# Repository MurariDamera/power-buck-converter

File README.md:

me · MD
# LM2596 Buck Converter — 12 V → 5 V
 
A fixed-output 5 V step-down (buck) converter built around the **LM2596T-5.0** switching regulator, designed in **KiCad 10**. Two-layer through-hole board, 71 × 45 mm, with ground pours on both layers and four M3 mounting holes.
 
This is a prototype design reproduced from a LM2596 design guide. It passes KiCad's electrical and design-rule checks, and the power stage has been verified in LTspice against TI's transient model (see [Simulation](#simulation)) — but it has **not** been prototyped or thermally tested. See [Operating limits](#operating-limits) before building.
 
## Design summary
 
| Parameter | Value |
| --- | --- |
| Regulator | LM2596T-5.0 (fixed 5 V, 150 kHz) |
| Input | 12 V nominal |
| Output | 5 V |
| Output target | 3 A (design target, not a validated rating) |
| Board | 71 × 45 mm, 2 layers, 1.6 mm nominal |
| Mounting | 4 × 3.2 mm M3 holes |
 
Power tracks are 1.25–1.5 mm with a short 0.9 mm switch-pin escape. Both copper layers have GND zones. A 0.35 mm bottom-layer trace carries feedback directly from C3's positive pad. U1 sits near the top edge to allow an external heatsink (heatsink not yet selected).
 
## Bill of materials
 
| Ref | Value | Footprint |
| --- | --- | --- |
| U1 | LM2596T-5.0 | TO-220-5 staggered (Package_TO_SOT_THT) |
| J1 | 12 V input | Phoenix MKDS 5.08 mm 1×02 |
| J2 | 5 V output | Phoenix MKDS 5.08 mm 1×02 |
| C1 | 680 µF / 35 V | CP_Radial D10 mm P5 mm |
| C2 | 100 nF / 50 V | C_Disc D5 mm P5 mm |
| C3 | 220 µF / 25 V | CP_Radial D8 mm P3.5 mm |
| D1 | 1N5822 | DO-201AD P15.24 mm |
| L1 | 33 µH, Isat ≥ 3.5 A | L_Radial D12.5 mm P7 mm |
| H1–H4 | M3 mounting hole | MountingHole 3.2 mm |
 
C1/C2/C3 correspond to Cin/Cin2/Cout in the source guide. No adjustable-output divider is fitted.
 
## Connections
 
| Net | Connected pins |
| --- | --- |
| VIN | J1.1, C1.1, C2.1, U1.1 |
| SW | U1.2, D1.1 (cathode/band), L1.1 |
| +5V | L1.2, C3.1, J2.1, U1.4 (FB) |
| GND | J1.2, C1.2, C2.2, U1.3, U1.5, D1.2 (anode), C3.2, J2.2 |
 
J1 pin 1 is input positive; J2 pin 1 is output positive; both pin 2 terminals are ground. Follow the `+` markings on the electrolytic footprints and the cathode band on D1. U1 uses the staggered TO-220-5 footprint, not a straight five-pin footprint.
 
## Files
 
- `Buck_Converter.kicad_pro` — project file. Open this in KiCad, then double-click the schematic or PCB.
- `Buck_Converter.kicad_sch` — schematic.
- `Buck_Converter.kicad_pcb` — placed, routed board with filled ground zones.
- `sym-lib-table`, `fp-lib-table` — library tables (reference standard KiCad 10 libraries).
- `ltspice/` — LTspice validation of the power stage. `Buck_Converter_LTspice.asc` is the schematic (open it and hit Run); `LM2596_5P0_TRANS.lib` is TI's official LM2596-5.0 transient model, ported from PSpice syntax; `LM2596_5P0_TRANS.asy` is the matching symbol; `Buck_Converter_LTspice.plt` restores the plot panes. All four files must stay together in the same folder.
 
## Validation
 
KiCad 10.0.6 ERC and DRC (with zone refill and schematic parity) both report zero violations, zero unconnected items, and zero parity issues, with no rule exclusions.
 
These checks verify CAD connectivity and geometry only — no prototype measurement or thermal test has been performed.
 
## Simulation
 
The power stage (D1, L1, C1–C3) plus TI's official LM2596-5.0 PSpice transient model were simulated in LTspice (`ltspice/Buck_Converter_LTspice.asc`), 12 V in, 150 kHz switching, transient analysis to steady state:
 
| Load | Simulated output |
| --- | --- |
| 1 A (5 Ω) | 4.99 V |
| 3 A design target (1.667 Ω) | 4.31 V, 120 mV ripple |
 
At the 3 A design target the loop sags to 4.31 V instead of regulating to 5.0 V. This is a real result, not a simulation artifact — it was confirmed by checking that regulation is accurate at light load (1 A) and only degrades as load approaches the design target, consistent with [Operating limits](#operating-limits) already flagging 3 A as unvalidated. Treat 3 A as the point where this design's regulation margin runs out, not as a safe operating current.
 
This is a transient-model simulation, not a hardware measurement — it doesn't account for PCB parasitics, the specific 1N5822's real diode curve, or thermal effects.
 
## Operating limits
 
- **12 V nominal input only** — C1 (35 V) and D1 (40 V) don't support the guide's 7–40 V range.
- **3 A is an unvalidated target** — LTspice shows regulation sagging to 4.31 V at 3 A vs. 4.99 V at 1 A ([Simulation](#simulation)), and the 1N5822 falls short of TI's recommended 3.9 A diode rating at that load.
- Verify real part ratings/footprints before ordering, and bring the board up on a current-limited supply, unloaded first.
 
## Source
 
Reproduced from the LM2596 buck converter design guide, cross-referenced against the [Texas Instruments LM2596 datasheet, Rev. G](https://www.ti.com/lit/ds/symlink/lm2596.pdf) (§9.2.1 and §9.4).

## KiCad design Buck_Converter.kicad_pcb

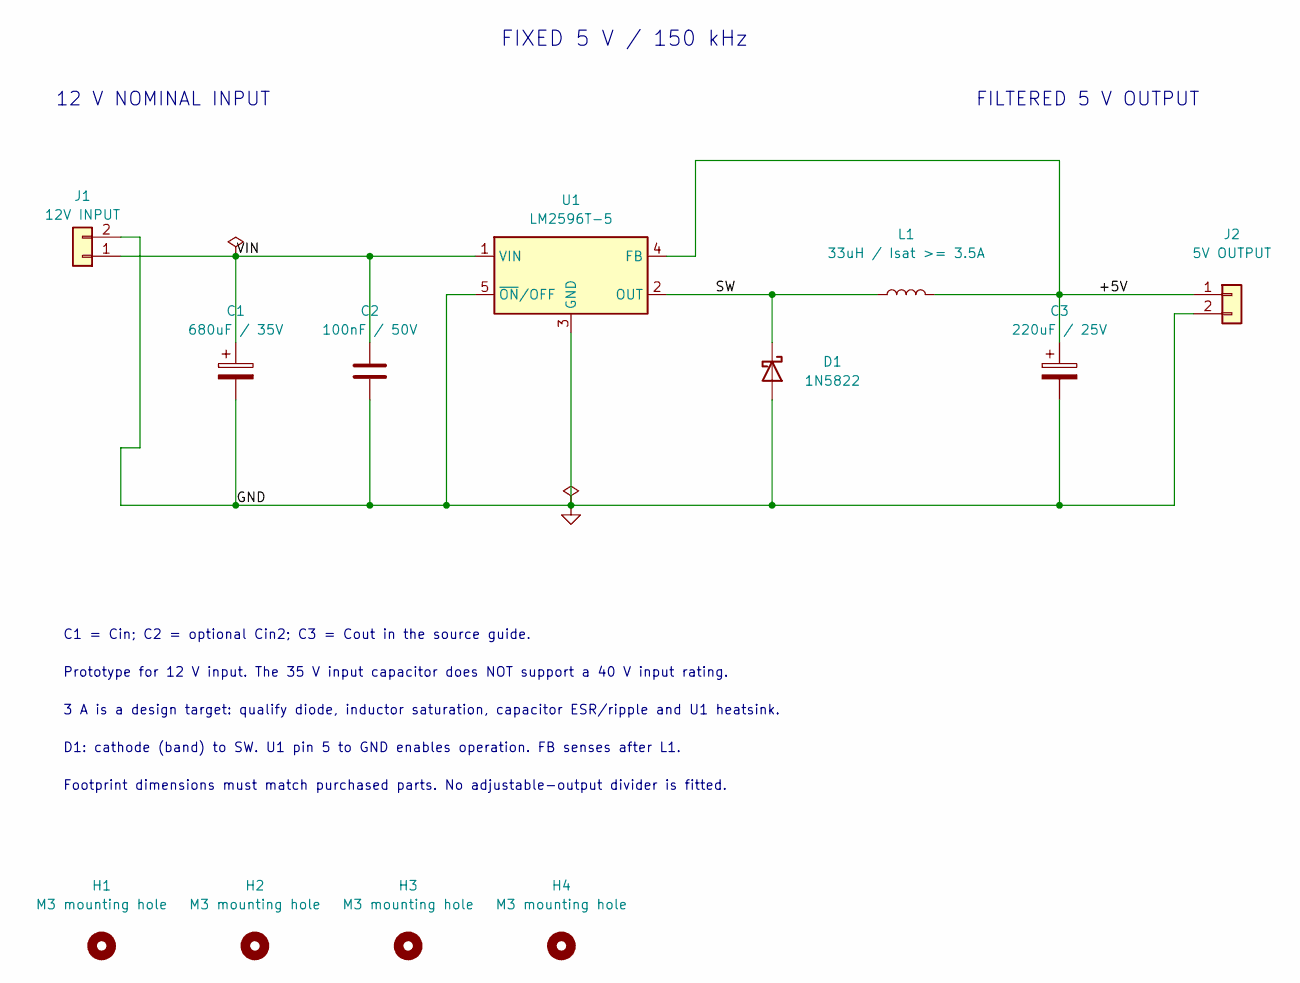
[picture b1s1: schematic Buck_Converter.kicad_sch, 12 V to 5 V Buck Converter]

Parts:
C1: 680uF / 35V; CP_Radial_D10.0mm_P5.00mm
C2: 100nF / 50V; C_Disc_D5.0mm_W2.5mm_P5.00mm
C3: 220uF / 25V; CP_Radial_D8.0mm_P3.50mm
D1: 1N5822; D_DO-201AD_P15.24mm_Horizontal
H1, H2, H3, H4: M3 mounting hole; MountingHole_3.2mm_M3
J1: 12V INPUT; TerminalBlock_Phoenix_MKDS-1,5-2-5.08_1x02_P5.08mm_Horizont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
J2: 5V OUTPUT; TerminalBlock_Phoenix_MKDS-1,5-2-5.08_1x02_P5.08mm_Horizont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
L1: 33uH / Isat >= 3.5A; L_Radial_D12.5mm_P7.00mm_Fastron_09HCP
U1: LM2596T-5; TO-220-5_P3.4x3.7mm_StaggerOdd_Lead3.8mm_Vertical

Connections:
/+5V: C3.1, J2.1, L1.2, U1.4 (FB)
/SW: D1.1 (K), L1.1, U1.2 (OUT)
/VIN: C1.1, C2.1, J1.1, U1.1 (VIN)
GND: C1.2, C2.2, C3.2, D1.2 (A), J1.2, J2.2, U1.3 (GND), U1.5 (~ON/OFF)

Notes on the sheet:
12 V NOMINAL INPUT
FIXED 5 V / 150 kHz
FILTERED 5 V OUTPUT
C1 = Cin; C2 = optional Cin2; C3 = Cout in the source guide.
Prototype for 12 V input. The 35 V input capacitor does NOT support a 40 V input rating.
3 A is a design target: qualify diode, inductor saturation, capacitor ESR/ripple and U1 heatsink.
D1: cathode (band) to SW. U1 pin 5 to GND enables operation. FB senses after L1.
Footprint dimensions must match purchased parts. No adjustable-output divider is fitted.

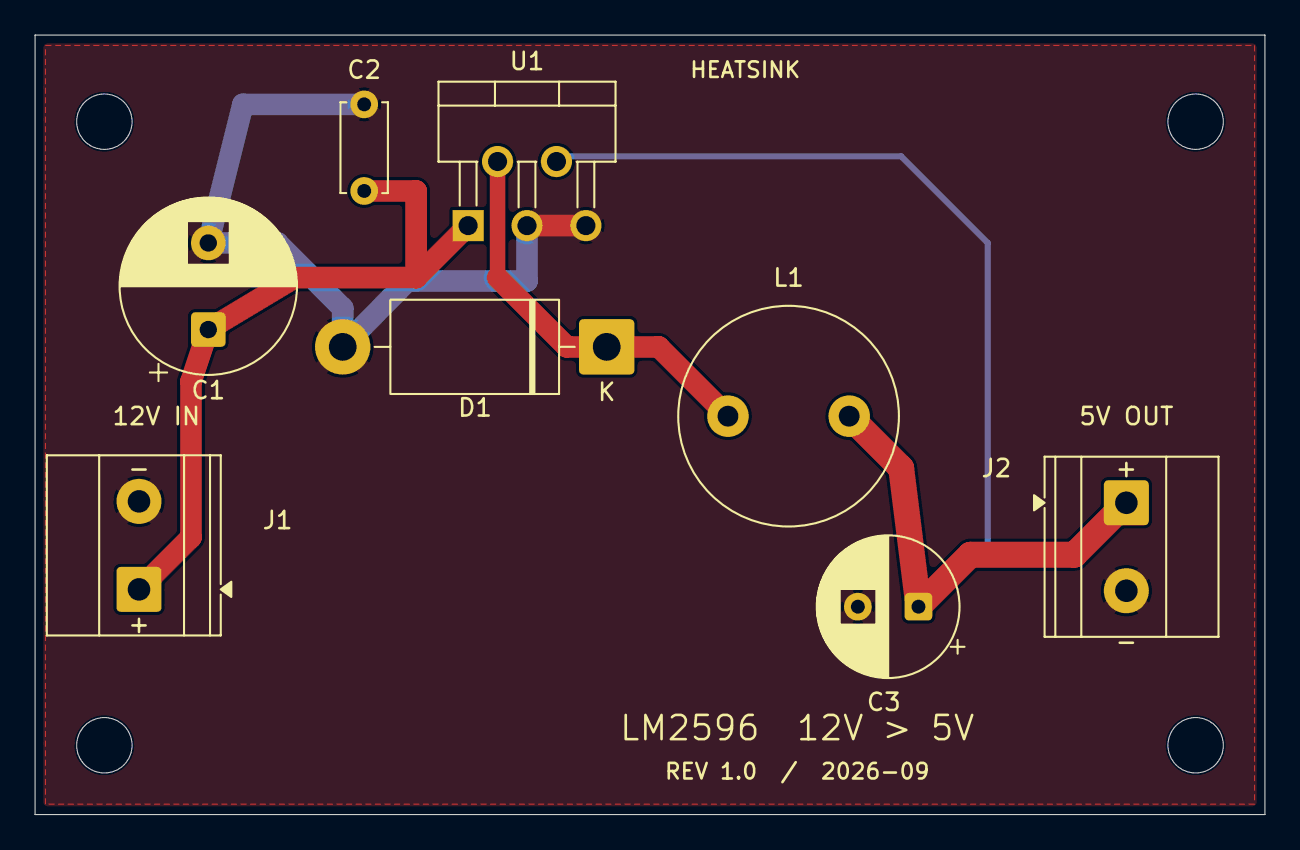
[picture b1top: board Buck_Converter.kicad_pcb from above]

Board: 2 copper layers, 71.0 x 45.0 mm, 12 parts (0 on the bottom side), 4 nets.
